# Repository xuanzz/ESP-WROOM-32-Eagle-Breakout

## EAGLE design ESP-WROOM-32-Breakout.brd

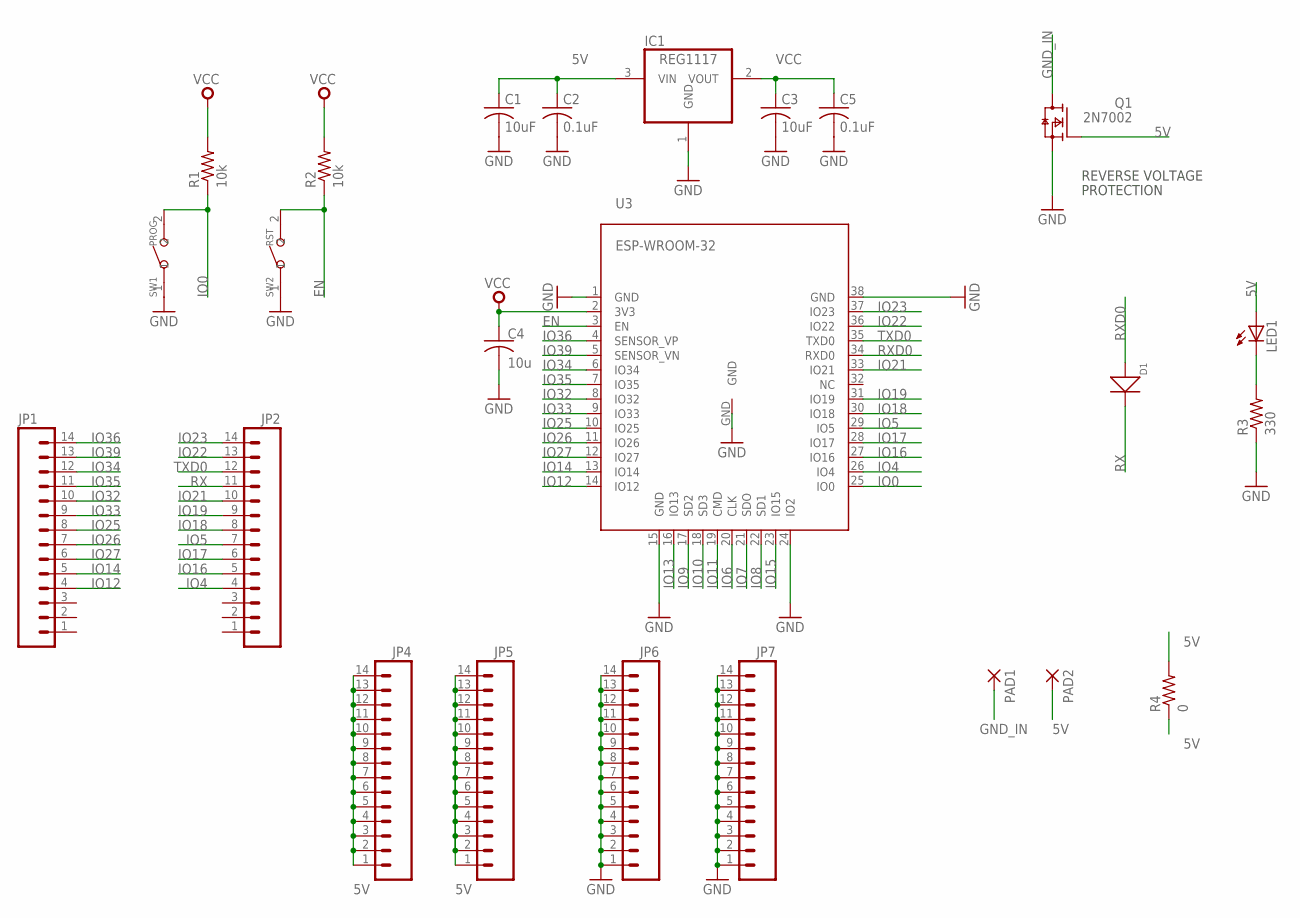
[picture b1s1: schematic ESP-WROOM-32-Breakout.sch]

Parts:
C1, C3: 10uF; C1206
C2, C5: 0.1uF; C1206
C4: 10u; C1206
D1: DIODE'0805'; SOD-323
IC1: REG1117; SOT223
JP1, JP2, JP4, JP5, JP6, JP7: M14; 1X14
LED1: LEDCHIPLED_1206; CHIPLED_1206
PAD1, PAD2: SMD5; SMD2,54-5,08
Q1: 2N7002; SOT23
R1, R2: 10k; R1206
R3: 330; R1206
R4: 0; R1206
SW1: PROG; SW2-4.0-6.0X3.0X2.5MM
SW2: RST; SW2-4.0-6.0X3.0X2.5MM
U3: ESP-WROOM-32

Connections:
5V: C1.1, C2.1, IC1.3 (VIN), JP4.1, JP4.2, JP4.3, JP4.4, JP4.5, JP4.6, JP4.7, JP4.8, JP4.9, JP4.10, JP4.11, JP4.12, JP4.13, JP4.14, JP5.1, JP5.2, JP5.3, JP5.4, JP5.5, JP5.6, JP5.7, JP5.8, JP5.9, JP5.10, JP5.11, JP5.12, JP5.13, JP5.14, LED1.A, PAD2.1, Q1.1 (G), R4.1, R4.2
EN: R2.1, SW2.2, U3.3 (EN)
GND: C1.2, C2.2, C3.2, C4.2, C5.2, IC1.1 (GND), JP6.1, JP6.2, JP6.3, JP6.4, JP6.5, JP6.6, JP6.7, JP6.8, JP6.9, JP6.10, JP6.11, JP6.12, JP6.13, JP6.14, JP7.1, JP7.2, JP7.3, JP7.4, JP7.5, JP7.6, JP7.7, JP7.8, JP7.9, JP7.10, JP7.11, JP7.12, JP7.13, JP7.14, Q1.2 (S), R3.1, SW1.1, SW2.1, U3.1 (GND), U3.15 (GND), U3.24 (IO2), U3.38 (GND), U3.GND
GND_IN: PAD1.1, Q1.3 (D)
IO0: R1.1, SW1.2, U3.25 (IO0)
IO4: JP2.4, U3.26 (IO4)
IO5: JP2.7, U3.29 (IO5)
IO6: U3.20 (CLK)
IO7: U3.21 (SDO)
IO8: U3.22 (SD1)
IO9: U3.17 (SD2)
IO10: U3.18 (SD3)
IO11: U3.19 (CMD)
IO12: JP1.4, U3.14 (IO12)
IO13: U3.16 (IO13)
IO14: JP1.5, U3.13 (IO14)
IO15: U3.23 (IO15)
IO16: JP2.5, U3.27 (IO16)
IO17: JP2.6, U3.28 (IO17)
IO18: JP2.8, U3.30 (IO18)
IO19: JP2.9, U3.31 (IO19)
IO21: JP2.10, U3.33 (IO21)
IO22: JP2.13, U3.36 (IO22)
IO23: JP2.14, U3.37 (IO23)
IO25: JP1.8, U3.10 (IO25)
IO26: JP1.7, U3.11 (IO26)
IO27: JP1.6, U3.12 (IO27)
IO32: JP1.10, U3.8 (IO32)
IO33: JP1.9, U3.9 (IO33)
IO34: JP1.12, U3.6 (IO34)
IO35: JP1.11, U3.7 (IO35)
IO36: JP1.14, U3.4 (SENSOR_VP)
IO39: JP1.13, U3.5 (SENSOR_VN)
unnamed: LED1.C, R3.2
RX: D1.-, JP2.11
RXD0: D1.+, U3.34 (RXD0)
TXD0: JP2.12, U3.35 (TXD0)
VCC: C3.1, C4.1, C5.1, IC1.2 (VOUT), R1.2, R2.2, U3.2 (3V3)

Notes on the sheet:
REVERSE VOLTAGE
PROTECTION

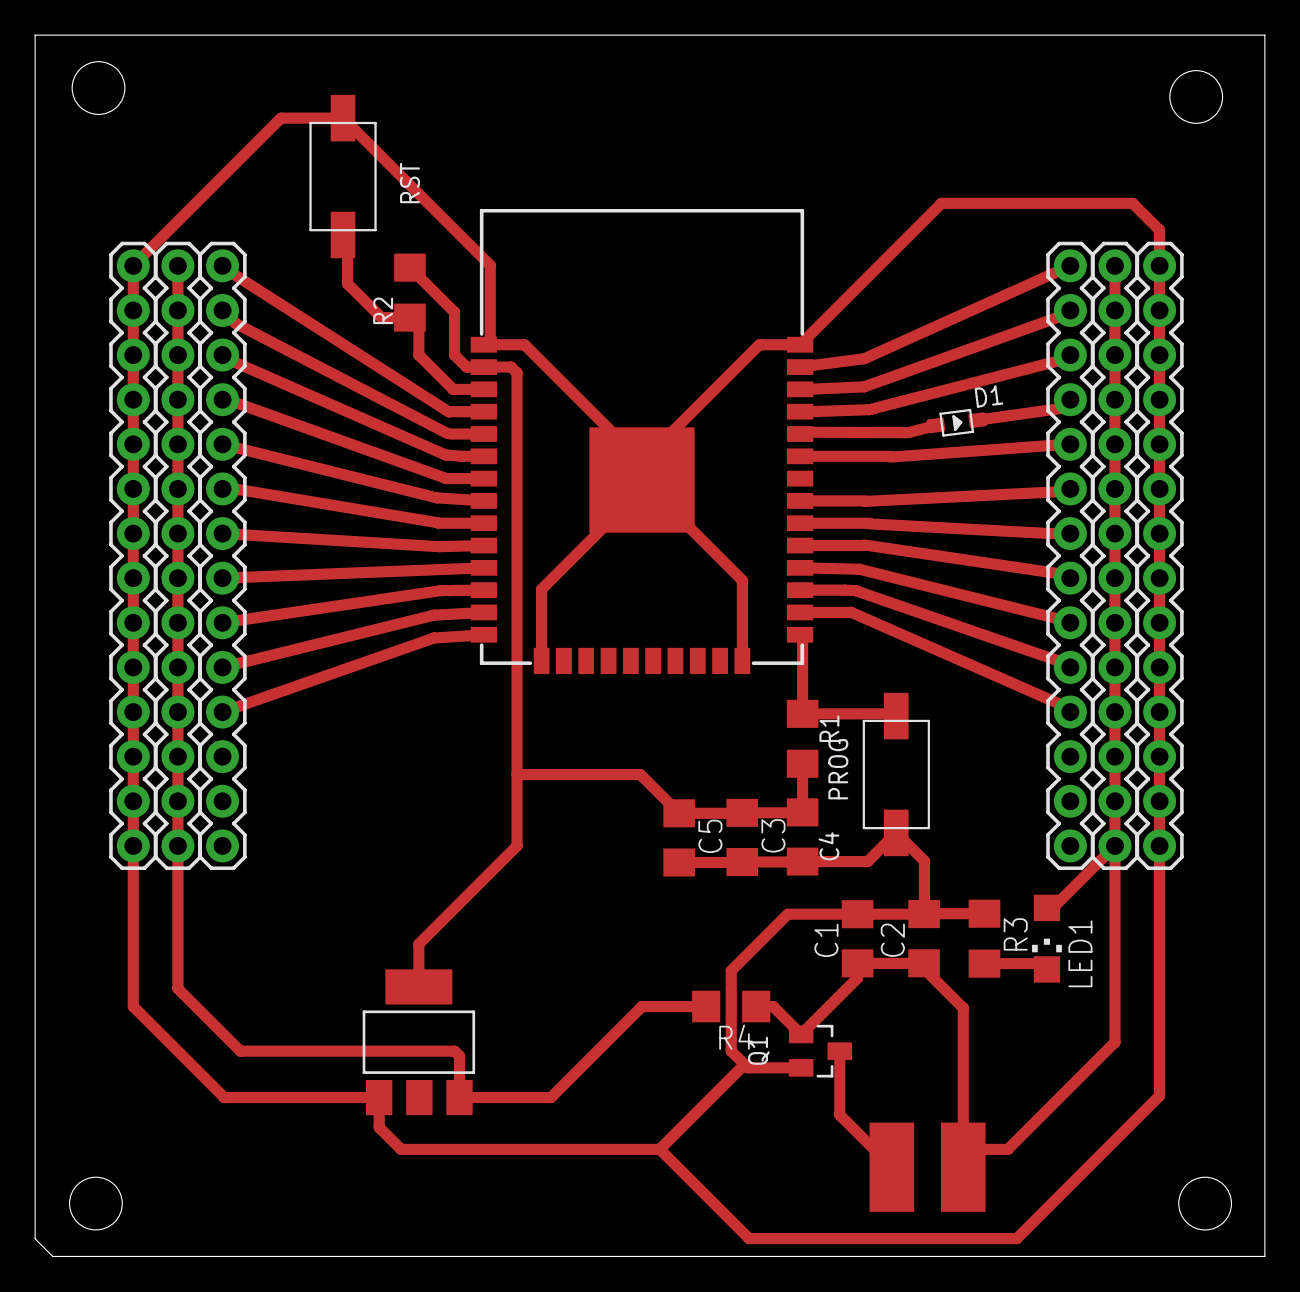
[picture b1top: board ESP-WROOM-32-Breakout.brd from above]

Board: 2 copper layers, 70.0 x 69.5 mm, 24 parts (0 on the bottom side), 30 nets.

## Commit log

2021-05-03 Updated layout, added 3,3V regulators

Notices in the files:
parts and their libraries:
SparkFun-Connectors: Licensing: Creative Commons ShareAlike 4.0 International - https://creativecommons.org/licenses/by-sa/4.0
